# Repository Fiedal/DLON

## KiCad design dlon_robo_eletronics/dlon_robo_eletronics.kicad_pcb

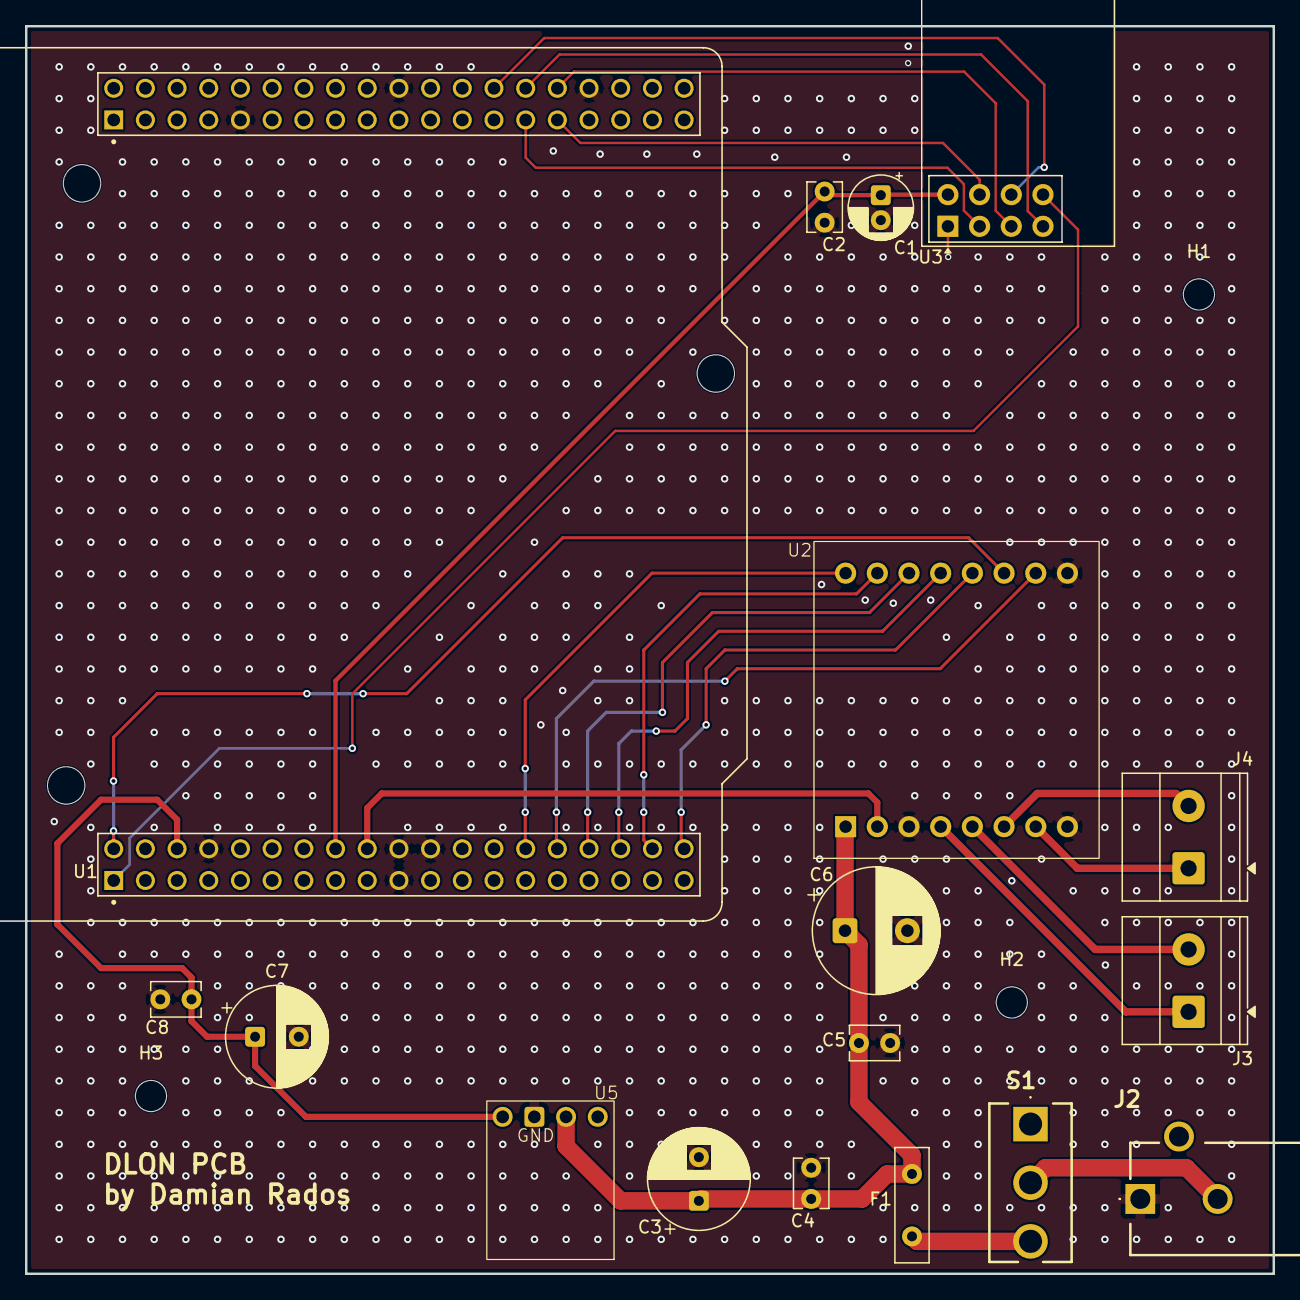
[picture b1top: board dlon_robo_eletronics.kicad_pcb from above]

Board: 2 copper layers, 100.0 x 100.0 mm, 20 parts (0 on the bottom side), 24 nets.

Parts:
C1: 10uF; CP_Radial_D5.0mm_P2.00mm
C2, C4, C5, C8: 100nF; C_Disc_D3.8mm_W2.6mm_P2.50mm
C3, C7: 100uF; CP_Radial_D8.0mm_P3.50mm
C6: 470uF; CP_Radial_D10.0mm_P5.00mm
F1: Polyfuse; C_Disc_D9.0mm_W2.5mm_P5.00mm
H1, H2, H3: MountingHole; MountingHole_2.5mm
J2: FC681465P__DC-10LP_; FC681465PDC10LP
J3, J4: Screw_Terminal_01x02; TerminalBlock_Phoenix_MKDS-1,5-2_1x02_P5.00mm_Horizontal
S1: SL19-121; SL19121
U1: NUCLEO-F446RE; MODULE_NUCLEO-F446RE_without_arduino
U2: D24V5F5; KAmod-TB6612FNG_footprint
U3: NRF24L01_Breakout; nRF24L01_Breakout
U5: Polulu_D24V5Fx

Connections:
+3V3: C1.1, C2.1, U1.CN7_16 (CN7_+3V3), U3.2 (VCC)
+5V: U1.CN7_18 (CN7_+5V), U2.1 (VCC)
/Motors_Driver/AIN1: U1.CN7_32 (PA4), U2.10 (AIN1)
/Motors_Driver/AIN2: U1.CN7_36 (PC1/PB9), U2.9 (AIN2)
/Motors_Driver/AO1: J3.1, U2.3 (A01)
/Motors_Driver/AO2: J3.2, U2.4 (AO2)
/Motors_Driver/BIN1: U1.CN7_38 (PC0/PB8), U2.12 (BIN1)
/Motors_Driver/BIN2: U1.CN7_2 (PC11), U2.13 (BIN2)
/Motors_Driver/BO1: J4.1, U2.6 (BO1)
/Motors_Driver/BO2: J4.2, U2.5 (B02)
/Motors_Driver/PWMA: U1.CN7_28 (PA0), U2.8 (PWMA)
/Motors_Driver/PWMB: U1.CN7_30 (PA1), U2.14 (PWMB)
/Motors_Driver/STBY: U1.CN7_34 (PB0), U2.11 (STBY)
/Nucleo-F446RE/5V_Nucleo: C7.1, C8.1, U1.CN7_6 (E5V), U5.1 (VOUT)
/Nucleo-F446RE/CE: U1.CN10_27 (PB4), U3.3 (CE)
/Nucleo-F446RE/IRQ: U1.CN7_1 (PC10), U3.8 (IRQ)
/Nucleo-F446RE/MISO: U1.CN10_28 (PB14), U3.7 (MISO)
/Nucleo-F446RE/MOSI: U1.CN10_26 (PB15), U3.6 (MOSI)
/Nucleo-F446RE/SCK: U1.CN10_30 (PB13), U3.5 (SCK)
/Nucleo-F446RE/~CSN: U1.CN10_29 (PB5), U3.4 (~CSN)
GND: C1.2, C2.2, C3.2, C4.2, C5.2, C6.2, C7.2, C8.2, J2.1 (SLEEVE), U1.CN7_8 (CN7_GND), U1.CN7_19 (CN7_GND), U1.CN7_20 (CN7_GND), U1.CN7_22 (CN7_GND), U1.CN10_9 (CN10_GND), U1.CN10_20 (CN10_GND), U1.CN10_32 (AGND), U2.2 (GND), U2.7 (GND), U2.15 (GND), U3.1 (GND), U5.2 (GND)
unnamed: F1.1, S1.3
unnamed: J2.3 (TIP), S1.2
VM: C3.1, C4.1, C5.1, C6.1, F1.2, U2.0 (VM), U5.3 (VIN)

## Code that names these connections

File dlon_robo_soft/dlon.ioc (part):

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Mcu.Name=STM32F446R(C-E)Tx
Mcu.Package=LQFP64
Mcu.UserName=STM32F446RETx
PA0-WKUP.GPIOParameters=GPIO_Label
PA0-WKUP.GPIO_Label=PWM1
PA0-WKUP.Signal=S_TIM2_CH1_ETR
PA1.GPIOParameters=GPIO_Label
PA1.GPIO_Label=PWM2
PA1.Signal=S_TIM2_CH2
PA13.GPIOParameters=GPIO_Label
PA13.GPIO_Label=TMS
PA13.Mode=Trace_Asynchronous_SW
PA13.Signal=SYS_JTMS-SWDIO
PA14.GPIOParameters=GPIO_Label
PA14.GPIO_Label=TCK
PA14.Mode=Trace_Asynchronous_SW
PA14.Signal=SYS_JTCK-SWCLK
PA4.GPIOParameters=GPIO_Label
PA4.GPIO_Label=AIN1_BRD
PA4.Signal=GPIO_Output
PA5.Signal=GPIO_Output
PB0.GPIOParameters=GPIO_Label
PB0.GPIO_Label=STBY_BRD
PB0.Signal=GPIO_Output
PB13.GPIOParameters=GPIO_Label
PB13.GPIO_Label=SPI_SCK
PB13.Mode=Full_Duplex_Master
PB13.Signal=SPI2_SCK
PB14.GPIOParameters=GPIO_Label
PB14.GPIO_Label=SPI_MISO
PB14.Mode=Full_Duplex_Master
PB14.Signal=SPI2_MISO
PB15.GPIOParameters=GPIO_Label
PB15.GPIO_Label=SPI_MOSI
PB15.Mode=Full_Duplex_Master
PB15.Signal=SPI2_MOSI
PB3.GPIOParameters=GPIO_Label
PB3.GPIO_Label=SWO
PB3.Mode=Trace_Asynchronous_SW
PB3.Signal=SYS_JTDO-SWO
PB4.GPIOParameters=GPIO_Label
PB4.GPIO_Label=CE_RADIO
PB4.Signal=GPIO_Output
PB5.GPIOParameters=PinState,GPIO_Label
PB5.GPIO_Label=CSN_RADIO
PB5.PinState=GPIO_PIN_SET
PB5.Signal=GPIO_Output
PC0.GPIOParameters=GPIO_Label
PC0.GPIO_Label=BIN1_BRD
PC0.Signal=GPIO_Output
PC1.GPIOParameters=GPIO_Label
PC1.GPIO_Label=AIN2_BRD
PC1.Signal=GPIO_Output
PC10.GPIOParameters=GPIO_PuPd,GPIO_Label,GPIO_ModeDefaultEXTI
PC10.GPIO_Label=IT_RADIO
PC10.GPIO_ModeDefaultEXTI=GPIO_MODE_IT_FALLING
PC10.GPIO_PuPd=GPIO_PULLUP
PC10.Signal=GPXTI10
PC11.GPIOParameters=GPIO_Label
PC11.GPIO_Label=BIN2_BRD
PC11.Signal=GPIO_Output
PC13.Signal=GPXTI13
RCC.HSE_VALUE=8000000
RCC.SYSCLKFreq_VALUE=180000000
RCC.SYSCLKSource=RCC_SYSCLKSOURCE_PLLCLK
board=NUCLEO-F446RE
boardIOC=true
